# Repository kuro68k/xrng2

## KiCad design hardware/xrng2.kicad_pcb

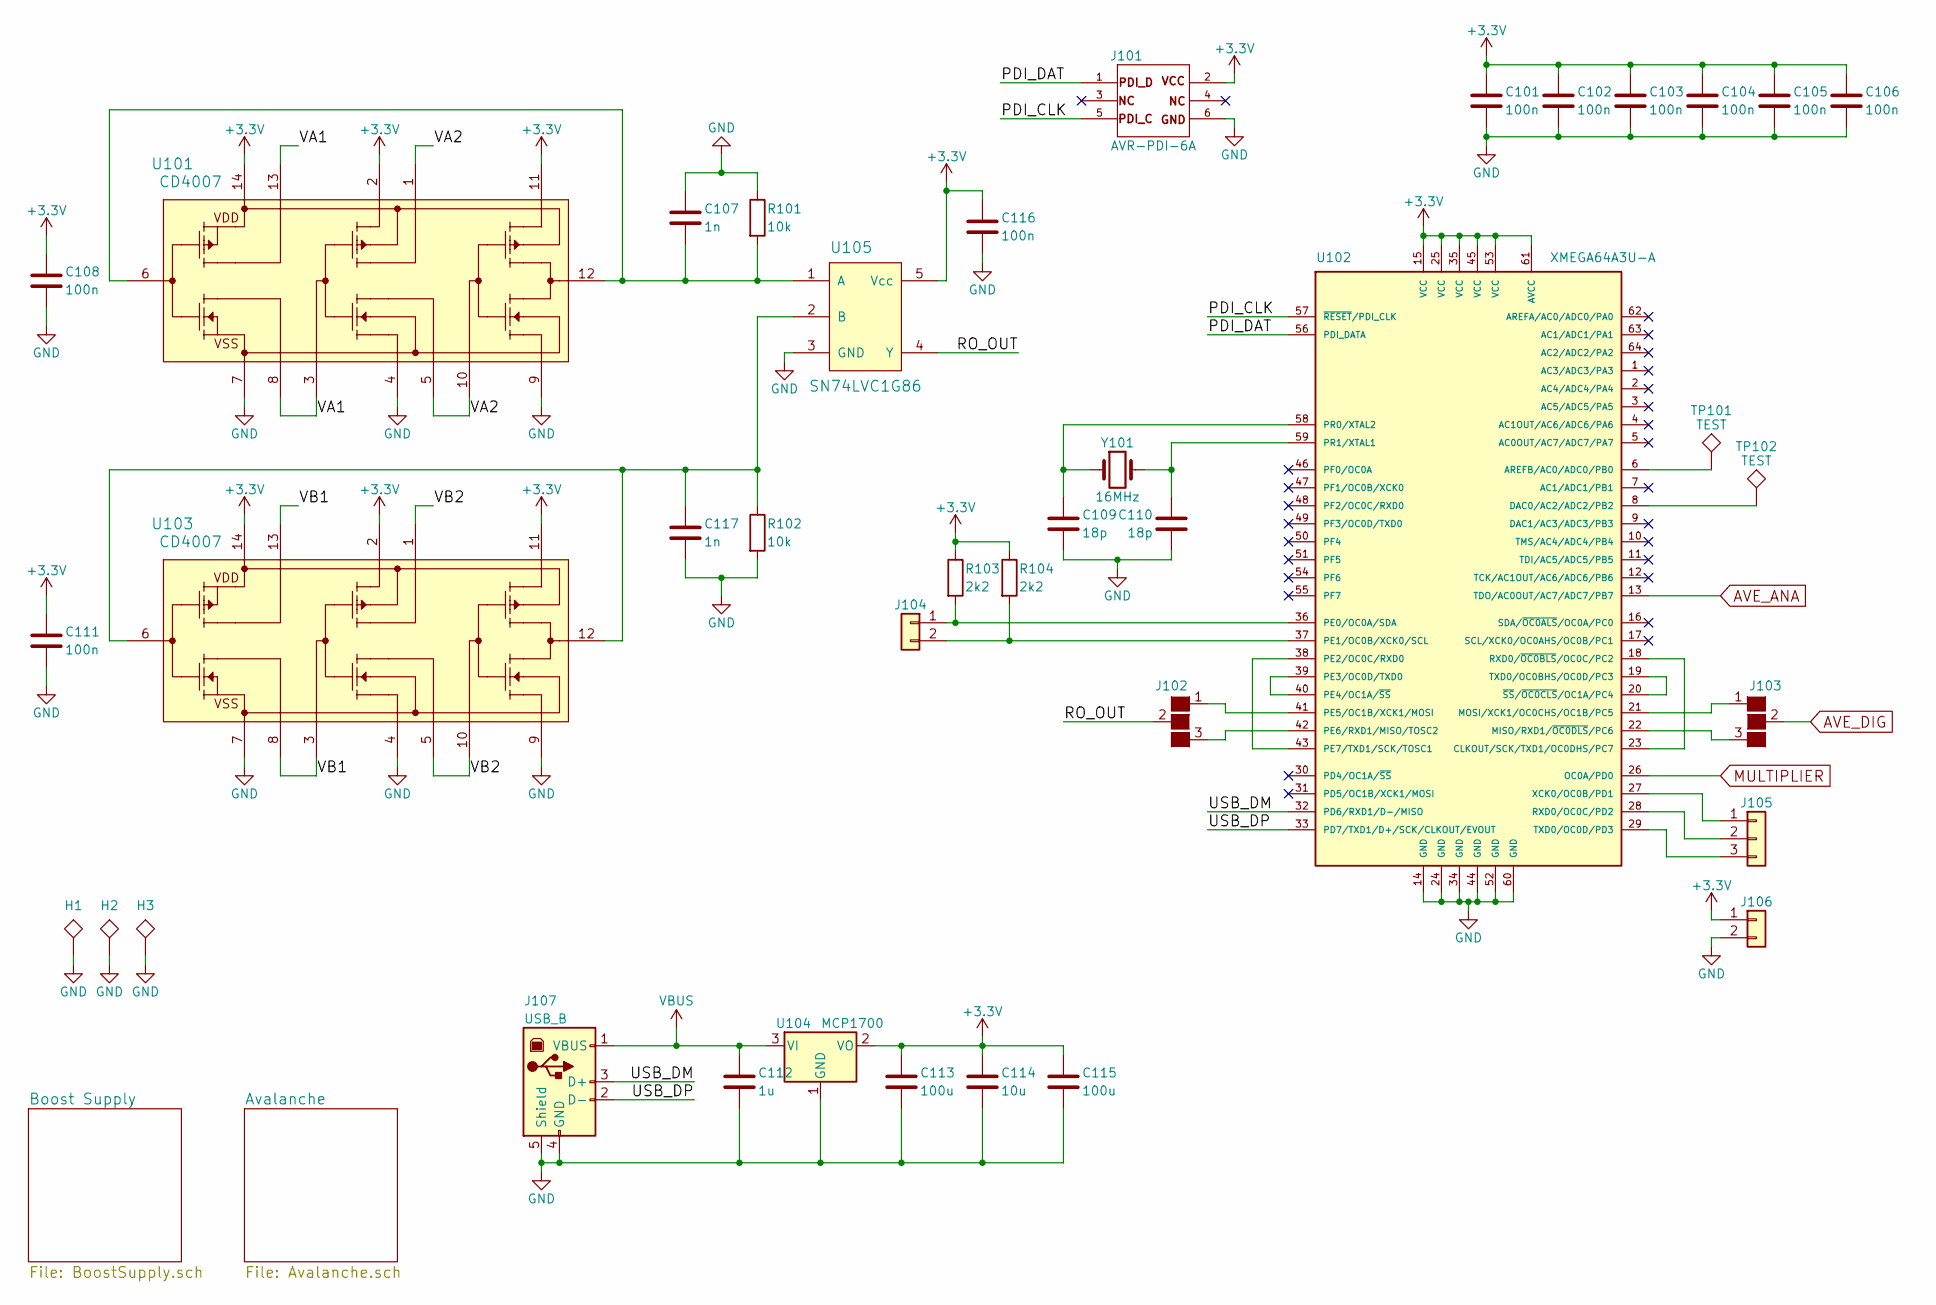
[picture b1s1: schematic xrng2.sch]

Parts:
C101, C102, C103, C104, C105, C106, C108, C111, C116: 100n; C_0603_HandSoldering
C107, C117: 1n; C_0603_HandSoldering
C109, C110: 18p; C_0603_HandSoldering
C112: 1u; C_0603_HandSoldering
C113: 100u; C_0603_HandSoldering
C114: 10u; C_0603_HandSoldering
C115: 100u; C_0805_HandSoldering
H1, H2, H3: MOUNT; MountingHole_3.2mm_M3
J101: AVR-PDI-6A; Pin_Header_Straight_2x03_Pitch2.54mm
J102, J103: GS3
J104, J106: Conn_01x02; Pin_Header_Straight_1x02_Pitch2.54mm
J105: Conn_01x03; Pin_Header_Straight_1x03_Pitch2.54mm
J107: USB_B
R101, R102: 10k; R_0603_HandSoldering
R103, R104: 2k2; R_0603_HandSoldering
TP101, TP102: TEST; Measurement_Point_Square-SMD-Pad_Big
U101, U103: CD4007; SOIC-14_3.9x8.7mm_Pitch1.27mm
U102: XMEGA64A3U-A; TQFP-64_14x14mm_Pitch0.8mm
U104: MCP1700; SOT-23
U105: SN74LVC1G86; SOT-23-5
Y101: 16MHz; SMD_Crystal_Multi_QC6CB_7A_ABM7

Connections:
+3V3: C101.1, C102.1, C103.1, C104.1, C105.1, C106.1, C108.1, C111.1, C113.1, C114.1, C115.1, C116.1, J101.2, J106.1, R103.1, R104.1, U101.2 (2Sp), U101.11 (3Sp), U101.14 (VDD), U102.15 (VCC), U102.25 (VCC), U102.35 (VCC), U102.45 (VCC), U102.53 (VCC), U102.61 (AVCC), U103.2 (2Sp), U103.11 (3Sp), U103.14 (VDD), U104.2 (VO), U105.5 (Vcc); also elsewhere on the board
/PDI_CLK: J101.5, U102.57 (~RESET~/PDI_CLK)
/PDI_DAT: J101.1, U102.56 (PDI_DATA)
/RO_OUT: J102.2 (G2), U105.4 (Y)
/USB_DM: J107.3 (D+), U102.32 (PD6/RXD1/D-/MISO)
/USB_DP: J107.2 (D-), U102.33 (PD7/TXD1/D+/SCK/CLKOUT/EVOUT)
/VA1: U101.3 (2A), U101.8 (1Dn), U101.13 (1Dp)
/VA2: U101.1 (2Dp), U101.5 (2Dn), U101.10 (3A)
/VB1: U103.3 (2A), U103.8 (1Dn), U103.13 (1Dp)
/VB2: U103.1 (2Dp), U103.5 (2Dn), U103.10 (3A)
AVE_ANA: U102.13 (TDO/AC0OUT/AC7/ADC7/PB7); also elsewhere on the board
AVE_DIG: J103.2 (G2); also elsewhere on the board
GND: C101.2, C102.2, C103.2, C104.2, C105.2, C106.2, C107.1, C108.2, C109.2, C110.2, C111.2, C112.2, C113.2, C114.2, C115.2, C116.2, C117.2, H1.1, H2.1, H3.1, J101.6, J106.2, J107.4 (GND), J107.5 (Shield), R101.1, R102.2, U101.4 (2Sn), U101.7 (VSS), U101.9 (3Sn), U102.14 (GND), U102.24 (GND), U102.34 (GND), U102.44 (GND), U102.52 (GND), U102.60 (GND), U103.4 (2Sn), U103.7 (VSS), U103.9 (3Sn), U104.1 (GND), U105.3 (GND); also elsewhere on the board
MULTIPLIER: U102.26 (OC0A/PD0); also elsewhere on the board
unnamed: C107.2, R101.2, U101.6 (1A), U101.12 (3Y), U105.1 (A)
unnamed: C109.1, U102.58 (PR0/XTAL2), Y101.1
unnamed: C110.1, U102.59 (PR1/XTAL1), Y101.2
unnamed: C117.1, R102.1, U103.6 (1A), U103.12 (3Y), U105.2 (B)
unnamed: J102.1 (G1), U102.41 (PE5/OC1B/XCK1/MOSI)
unnamed: J102.3 (G3), U102.42 (PE6/RXD1/MISO/TOSC2)
unnamed: J103.1 (G1), U102.21 (MOSI/XCK1/OC0CHS/OC1B/PC5)
unnamed: J103.3 (G3), U102.22 (MISO/RXD1/~OC0DLS~/PC6)
unnamed: J104.1, R103.2, U102.36 (PE0/OC0A/SDA)
unnamed: J104.2, R104.2, U102.37 (PE1/OC0B/XCK0/SCL)
unnamed: J105.1, U102.27 (XCK0/OC0B/PD1)
unnamed: J105.2, U102.28 (RXD0/OC0C/PD2)
unnamed: J105.3, U102.29 (TXD0/OC0D/PD3)
unnamed: TP101.1, U102.6 (AREFB/AC0/ADC0/PB0)
unnamed: TP102.1, U102.8 (DAC0/AC2/ADC2/PB2)
unnamed: U102.18 (RXD0/~OC0BLS~/OC0C/PC2), U102.23 (CLKOUT/SCK/TXD1/OC0DHS/PC7)
unnamed: U102.19 (TXD0/OC0BHS/OC0D/PC3), U102.20 (~SS~/~OC0CLS~/OC1A/PC4)
unnamed: U102.38 (PE2/OC0C/RXD0), U102.43 (PE7/TXD1/SCK/TOSC1)
unnamed: U102.39 (PE3/OC0D/TXD0), U102.40 (PE4/OC1A/~SS~)
VBUS: C112.1, J107.1 (VBUS), U104.3 (VI); also elsewhere on the board

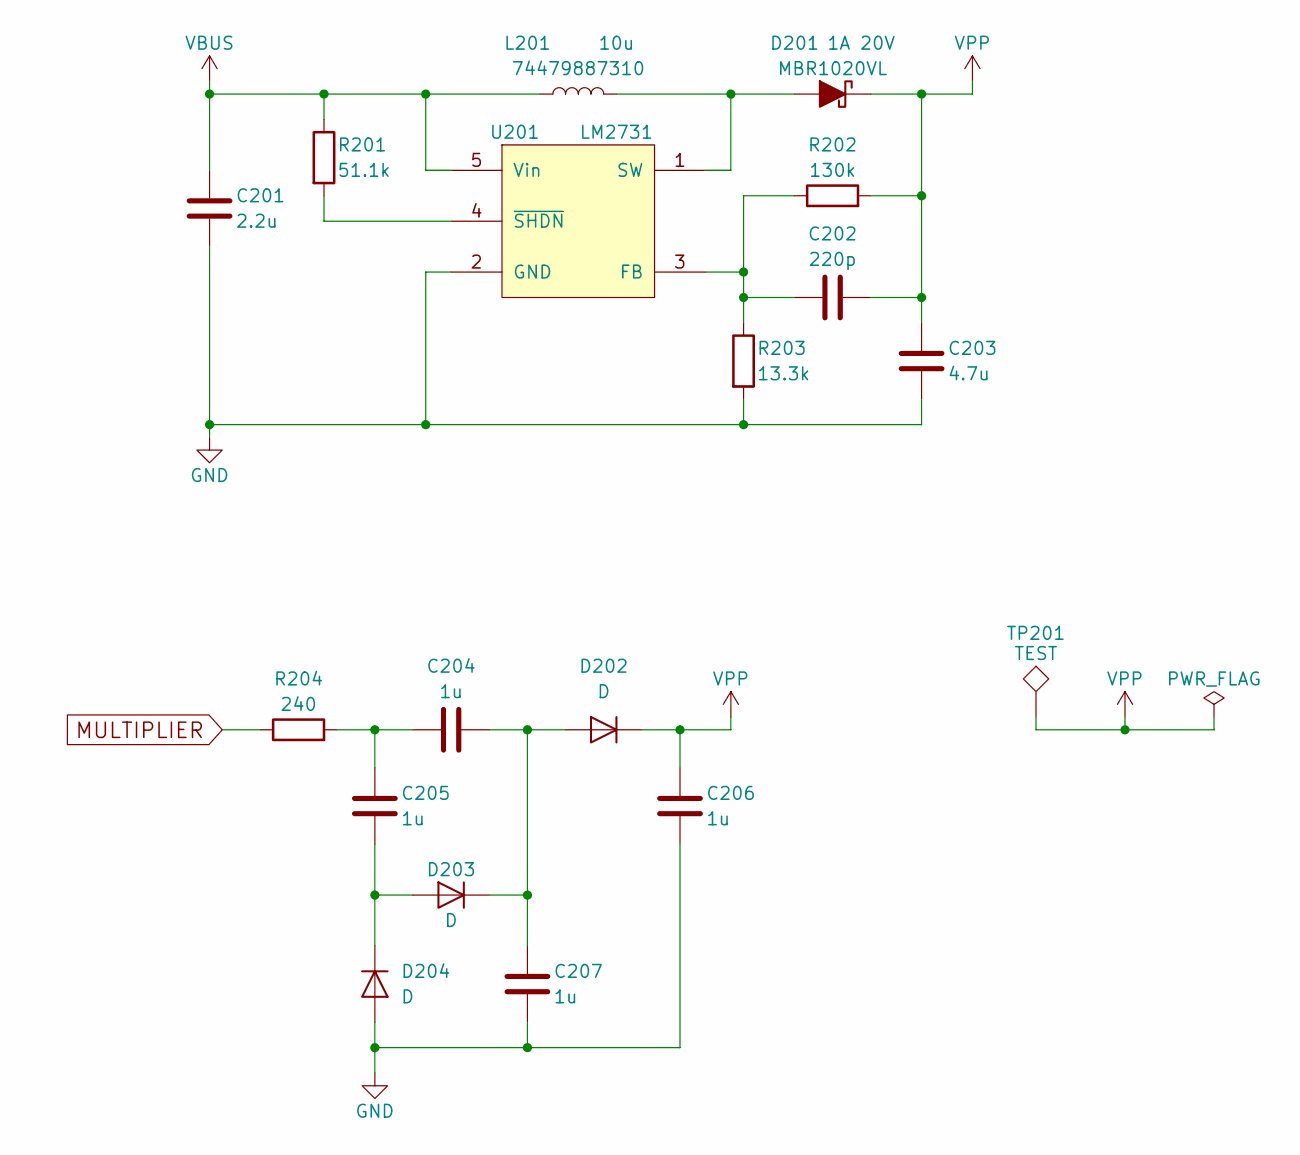
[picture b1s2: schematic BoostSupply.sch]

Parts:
C201: 2.2u; C_0603_HandSoldering
C202: 220p; C_0603_HandSoldering
C203: 4.7u; C_0805_HandSoldering
C204, C205, C206, C207: 1u; C_0603_HandSoldering
D201: 1A 20V; D_SOD-123F
D202, D203, D204: D; D_SOD-523
L201: 10u; R_0805_HandSoldering
R201: 51.1k; R_0603_HandSoldering
R202: 130k; R_0603_HandSoldering
R203: 13.3k; R_0603_HandSoldering
R204: 240; R_0603_HandSoldering
TP201: TEST; Measurement_Point_Square-SMD-Pad_Big
U201: LM2731; SOT-23-5

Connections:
GND: C201.2, C203.2, C206.2, C207.2, D204.2 (A), R203.2, U201.2 (GND); also elsewhere on the board
MULTIPLIER: R204.1; also elsewhere on the board
unnamed: C202.1, R202.1, R203.1, U201.3 (FB)
unnamed: C204.1, C205.1, R204.2
unnamed: C204.2, C207.1, D202.2 (A), D203.1 (K)
unnamed: C205.2, D203.2 (A), D204.1 (K)
unnamed: D201.2 (A), L201.1, U201.1 (SW)
unnamed: R201.2, U201.4 (~SHDN)
VBUS: C201.1, L201.2, R201.1, U201.5 (Vin); also elsewhere on the board
VPP: C202.2, C203.1, C206.1, D201.1 (K), D202.1 (K), R202.2, TP201.1; also elsewhere on the board

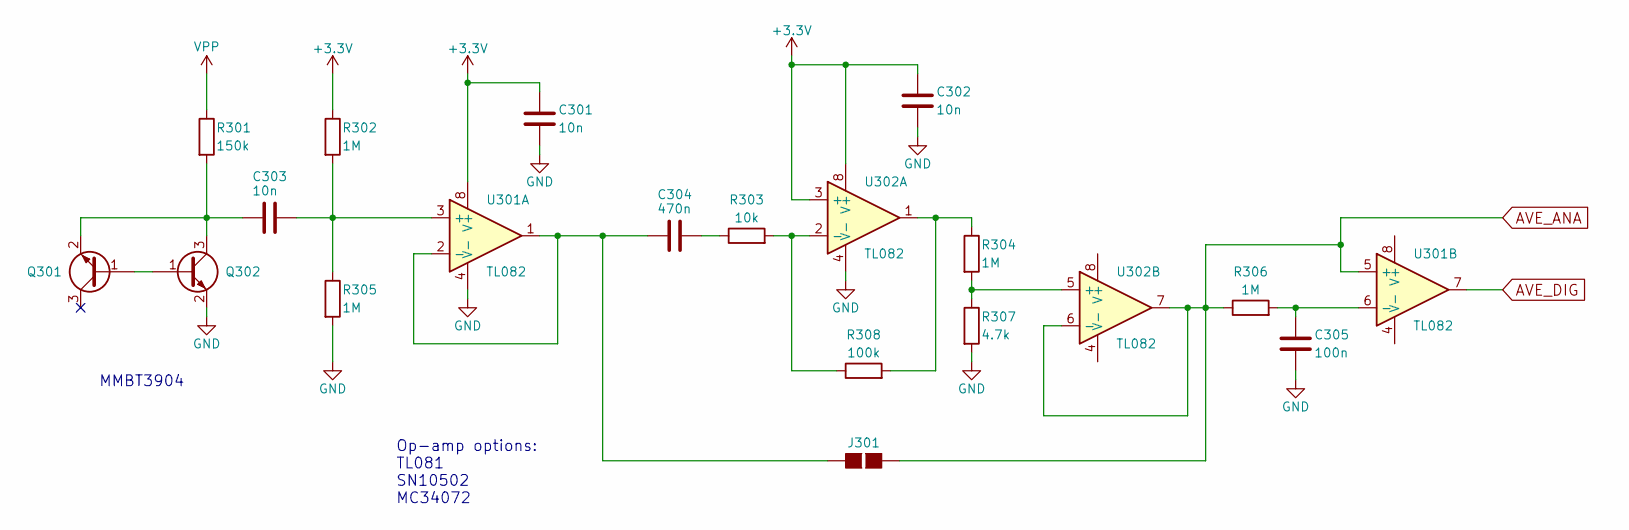
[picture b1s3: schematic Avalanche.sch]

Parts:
C301, C302, C303: 10n; C_0603_HandSoldering
C304: 470n; C_0603_HandSoldering
C305: 100n; C_0603_HandSoldering
J301: GS2
Q301, Q302: MMBT3904; SOT-23
R301: 150k; R_0603_HandSoldering
R302, R304, R305, R306: 1M; R_0603_HandSoldering
R303: 10k; R_0603_HandSoldering
R307: 4.7k; R_0603_HandSoldering
R308: 100k; R_0603_HandSoldering
U301, U302: TL082; SOIC-8_3.9x4.9mm_Pitch1.27mm

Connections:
+3V3: C301.1, C302.1, R302.1, U301.8 (V+), U302.3 (+), U302.8 (V+); also elsewhere on the board
AVE_ANA: J301.2 (G2), R306.1, U301.5 (+), U302.6 (-), U302.7; also elsewhere on the board
AVE_DIG: U301.7; also elsewhere on the board
GND: C301.2, C302.2, C305.2, Q302.2 (E), R305.2, R307.2, U301.4 (V-), U302.4 (V-); also elsewhere on the board
unnamed: C303.1, Q301.2 (E), Q302.3 (C), R301.2
unnamed: C303.2, R302.2, R305.1, U301.3 (+)
unnamed: C304.1, J301.1 (G1), U301.1, U301.2 (-)
unnamed: C304.2, R303.1
unnamed: C305.1, R306.2, U301.6 (-)
unnamed: Q301.1 (B), Q302.1 (B)
unnamed: R303.2, R308.1, U302.2 (-)
unnamed: R304.1, R308.2, U302.1
unnamed: R304.2, R307.1, U302.5 (+)
VPP: R301.1; also elsewhere on the board

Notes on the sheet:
MMBT3904
Op-amp options: TL081 SN10502 MC34072

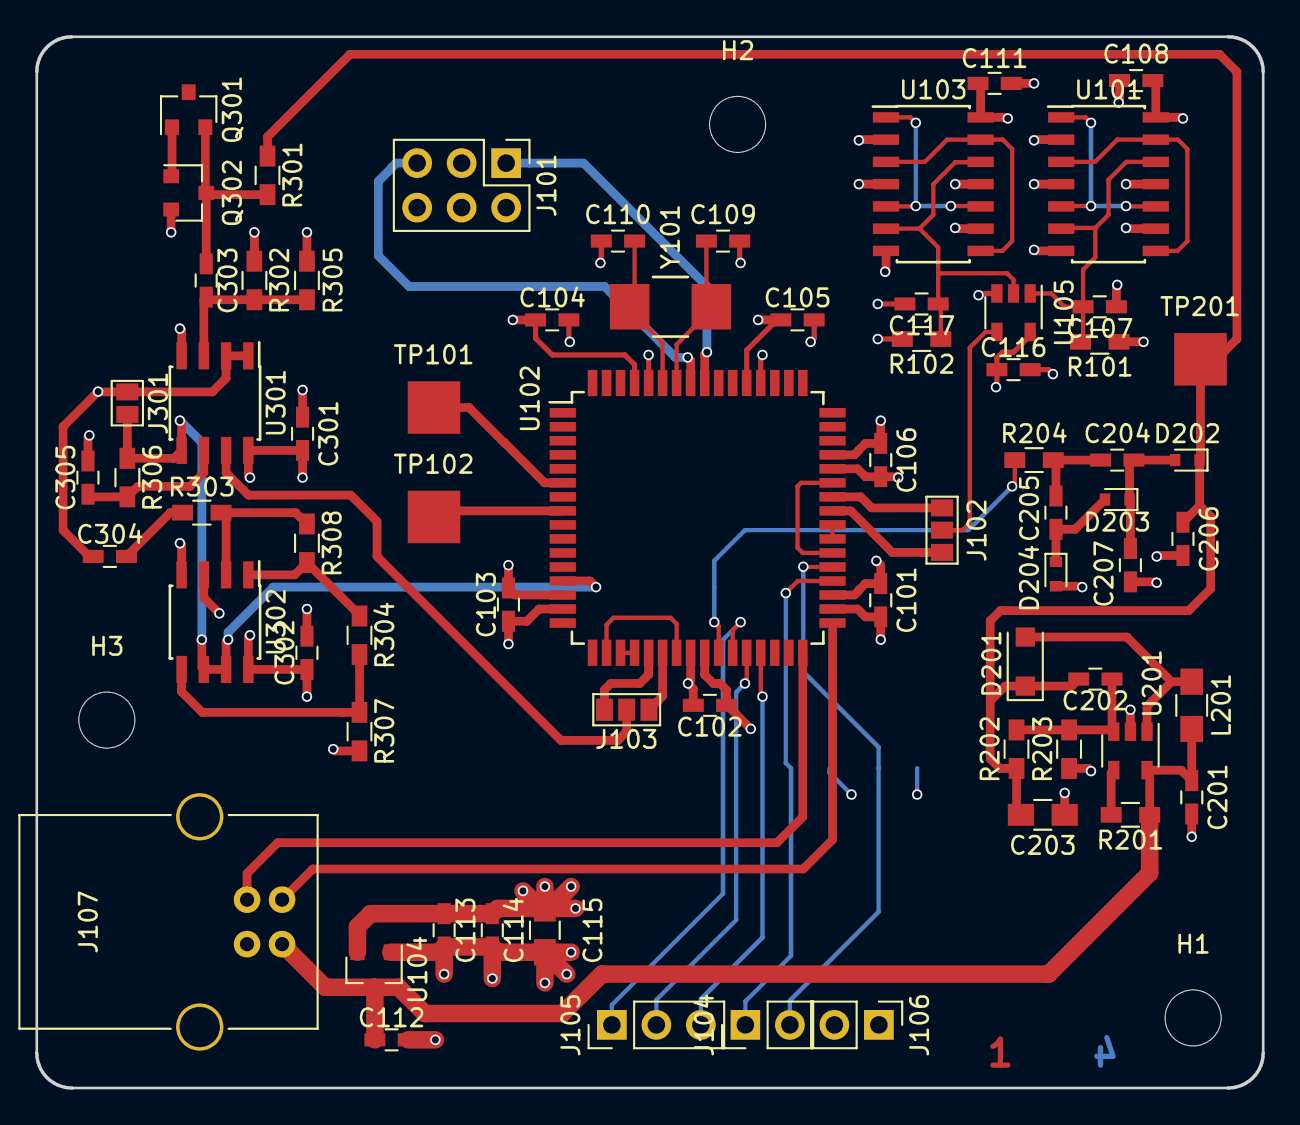
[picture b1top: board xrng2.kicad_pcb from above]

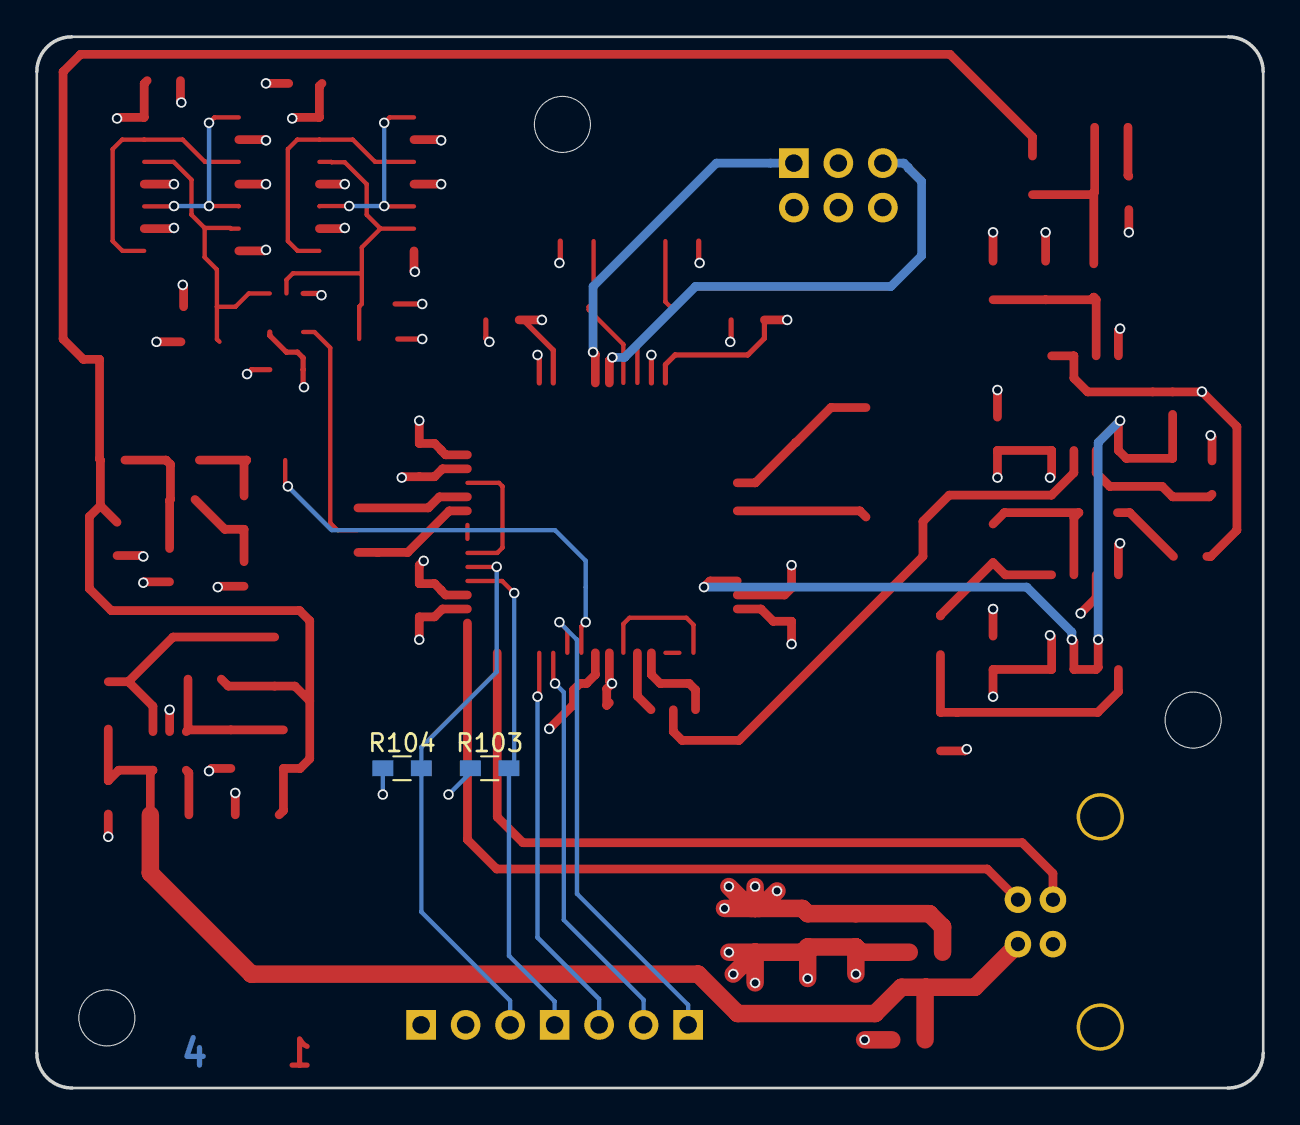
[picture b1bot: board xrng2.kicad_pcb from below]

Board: 4 copper layers, 70.0 x 60.0 mm, 75 parts (2 on the bottom side), 50 nets.

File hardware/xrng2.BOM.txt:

Title:      
Date:       21/06/2018 09:14:43
Source:     xrng2.sch
Revsision:  

No.  Reference             Value         Footprint                       Precision

[ Capacitors, 12 values, X7R/X5R, 16V unless otherwise stated ]
----------------------------------------------------------------------------------
9    C101, C102, C103      100n          0603                            
     C104, C105, C106
     C108, C111, C305
1    C107                  1n            0603                            
2    C109, C110            18p           0603                            
5    C112, C204, C205      1u            0603                            
     C206, C207
1    C113                  100u          0603                            
1    C114                  10u           0603                            
1    C115                  100u          0805                            
1    C201                  2.2u          0603                            
1    C202                  220p          0603                            
1    C203                  4.7u          0805                            
3    C301, C302, C303      10n           0603                            
1    C304                  470n          0603                            

[ Diodes, 3 values ]
----------------------------------------------------------------------------------
2    D101, D102            D_ALT         D_SOD-523                       
1    D201                  1A 20V        SOD-123                         
3    D202, D203, D204      D             D_SOD-523                       

[ H, 1 value ]
----------------------------------------------------------------------------------
3    H1, H2, H3            MOUNT         MountingHole_3.2mm_M3           

[ Connectors, 6 values ]
----------------------------------------------------------------------------------
1    J101                  AVR-PDI-6A    ...r_Straight_2x03_Pitch2.54mm  
2    J102, J103            GS3           GS3                             
2    J104, J106            Conn_01x02    ...r_Straight_1x02_Pitch2.54mm  
1    J105                  Conn_01x03    ...r_Straight_1x03_Pitch2.54mm  
1    J107                  USB_B         USB_B                           
1    J301                  GS2           GS2                             

[ Inductors, 1 value ]
----------------------------------------------------------------------------------
1    L201                  10u           0805                            

[ Transistors, 1 value ]
----------------------------------------------------------------------------------
2    Q301, Q302            MMBT3904      SOT-23                          

[ Resistors, 10 values, 1% unless otherwise stated ]
----------------------------------------------------------------------------------
3    R101, R102, R303      10k           0603                            
2    R103, R104            2k2           0603                            
1    R201                  51.1k         0603                            
1    R202                  130k          0603                            
1    R203                  13.3k         0603                            
1    R204                  240           0603                            
1    R301                  150k          0603                            
4    R302, R304, R305      1M            0603                            
     R306
1    R307                  4.7k          0603                            
1    R308                  100k          0603                            

[ Integrated Circuits, 5 values ]
----------------------------------------------------------------------------------
2    U101, U103            CD4007        SOIC-14_3.9x8.7mm_Pitch1.27mm   
1    U102                  XMEGA64A3U-A  TQFP-64_14x14mm_Pitch0.8mm      
1    U104                  MCP1700       SOT-23                          
1    U201                  LM2731        SOT-23                          
2    U301, U302            TL082         SOIC-8_3.9x4.9mm_Pitch1.27mm    

[ Crystals, 1 value ]
----------------------------------------------------------------------------------
1    Y101                  16MHz         QC6CB/7A/ABM7 crystals

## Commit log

2017-10-12 :circus_tent: Added .gitattributes
2018-06-18 Minimized balancing circuit
2018-06-18 Alternative to step up reg
2018-06-18 IDs, footprints, DRC
2018-06-18 Corrected ring oscillator wiring
2018-06-18 Design rules for Seeed
2018-06-18 Changed cap to 0805
2018-06-18 Sub circuit layouts
2018-06-18 Dimensions and layout
2018-06-18 Tracking finished
2018-06-19 DRC OK
2018-06-19 F.Fab clean-up
2018-06-19 Corrected layer for silk text
2018-06-19 I2C on expansion header
2018-06-19 Pull-ups for I2C
2018-06-19 I2C on expansion
2018-06-19 Silk labels
2018-06-19 Silkscreen outlines
2018-06-19 Outline corrections
2018-06-19 C112 outline
2018-06-19 Mounting holes
2018-06-19 Layer IDs
2018-06-19 ident text
2018-06-19 Remove plot
2018-06-19 Autosave
2018-06-19 Additional silk
2018-06-19 Rounded corners off
2018-06-21 Moved sims to new folder
2018-06-21 Added BOM (kibom)
2018-06-21 XOR mixer
2018-06-21 Footprint
2018-06-21 Corrected C113 value
2018-06-21 16V output parts
2018-08-16 PDF schematic
